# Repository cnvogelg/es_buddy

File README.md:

# es_buddy - EuroShield Add On Boards

EuroShield Buddy PCB Boards and Arduino Library.

  - [Teensy 4.0 Adapter](#teensy-40-adapter)
  - [Rotary Encoder Buddy Board](#rotary-encoder-buddy-board)
  - [LCD/OLED Display Buddy Board](#lcdoled-display-buddy-board)
  - [Twister Buddy Board](#twister-buddy-board)

You can combine these boards as you like.

Licensed by Creative Commons Attribution Share Alike 4.0 International

## Teensy 4.0 Adapter

Version: 1.1

This little adapter board allows to use a Teensy 4.0 board on your EuroShield 1 (short ES) eurorack module.

This is the required re-routing of the Pins:

| Teensy 3.x / EuroShield Pin | Teensy 4.x Pin | Description |
|-----------------------------|----------------|-------------|
| GND | GND | |
| 0 | 0 | Midi IN |
| 1 | 1 | Midi Out |
| 2 | 2 | Button on ES and on Rotary Encoder |
| 3 | 3 | LED 1 |
| 4 | 4 | LED 2 |
| 5 | 5 | LED 2 |
| 6 | 6 | LED 3 |
| 7 | 11 | SPI MOSI |
| 8 | 9 | Display Reset |
| 9 | 21 | Audio BCLK |
| 10 | 10 | SPI CS |
| 11 | 23 | Audio MCLK - A 100 Ohm Resistor is required here! |
| 12 | 12 | SPI MISO |

| Teensy 3.x / EuroShield Pin | Teensy 4.x Pin | Description |
|-----------------------------|----------------|-------------|
| VIN | VIN | |
| AGND | AGND | |
| 3.3V | 3.3V | |
| 23 | 20 | Audio LRCLK |
| 22 | 7 | Audio TX DIN |
| 21 | 15 | Lo Pot on ES |
| 20 | 14 | Hi Pot on ES |
| 19 | 19 | I2C SCL |
| 18 | 18 | I2C SDA |
| 17 | 17 | Rotary Encoder A |
| 16 | 16 | Rotary Encoder B |
| 15 | 22 | Display CMD/Data |
| 14 | 13 | SPI SCK |
| 13 | 8 | Audio RX DOUT |

All Pins are direclty connected expect Audio MCLK is connected via
a 100 Ohm resistor.

## Rotary Encoder Buddy Board

Version: 1.1

Add a rotary encoder with button to your Euroshield.

### BOM

| Symbol | Part | Description | Mouser No. |
|--------|------|-------------|------------|
| ROT1 | PEC12R-3220F-S0024 | Bourns Rotary Encoder | 652-PEC12R3220FS0024 |
| R1-R3 | SMD 0805 10k | 10k Resistor | 71-CRCW080510K0FKEAC |

## LCD/OLED Display Buddy Board

Version: 1.1

Add an SPI LCD or OLED display to your EuroShield. While the OLED with 
128 x 64 fits nicely into the form factor of the shield, the LCD is wider
and offers 160 x 128 colored pixels.

The LCD has the following parameters:

 - 160 x 128 color TFT LCD 1.8 Inch
 - SPI
 - ST 7735 Controller

| LCD Pin | Teensy 3.2 Pin | Description |
| ------- | ---------- | ----------- |
| 1 | GND | GND |
| 2 | 3.3V | 3.3V |
| 3 | 8  | Display Reset |
| 4 | 15 | Display Cmd/Data |
| 5 | -  | N/A |
| 6 | 10 | SPI CS |
| 7 | 7  | SPI MOSI |
| 8 | 14 | SPI SCK |
| 9 | 12 | SPI MISO |
| 10 | 3.3V | Display Light |

I use an Adafruit 1.8" Color TFT LCD display with MicroSD Card Breakout (358)

The OLED has the following parameters:

- 128 x 64 monochrome OLED 0.96 Inch
- SPI
- SSD 1306 Controller

| OLED Pin | Teensy 3.2 Pin | Description |
| ------- | ---------- | ----------- |
| 1 | 3.3V | 3.3V |
| 2 | GND | GND |
| 3 | -  | N/A|
| 4 | 7  | SPI MOSI |
| 5 | 14 | SPI SCK |
| 6 | 10 | SPI CS |
| 7 | 15 | Display Cmd/Data |
| 8 | 8  | Display Reset |

## Twister Buddy Board

Version: 1.0

Turn the Teensy around so that the USB connector points upwards and 
a connected USB cable gets out of the way and does not obstruct the display.

# Build Instructions

If you want to build the full stack of buddy boards:

1. Start with the display board and solder extra long header pins

2. First populate the rotary encoder board (resistors and the encoder) and 
  then solder the board below the display board

3. Prepare the Twister Board by adding headers to one side for a Teensy 4.0
  setup or a female connector for a Teensy 3.2. If you want to 
  use a Teensy 4.0 then add a female connector to the Teensy 4.0 side of the
  adapter:

4. Solder the prepared Twister Board on top of the Display Board. Make sure
  that the Teensy USB port on the top side points upwards:

5. For a Teensy 4.0 finally solder the Teensy 4.0 adapter board on top of
  the Twister Board. Note: make sure to add some space between the boards
  so that the Teensy 4.0 female connector pins do not touch the Display
  Board pins! Here a both variants: Teensy 4.0 and Teensy 3.2 boards

6. Finally add either a LCD or OLED display. Both display types work with 
  both Teensy CPUs.

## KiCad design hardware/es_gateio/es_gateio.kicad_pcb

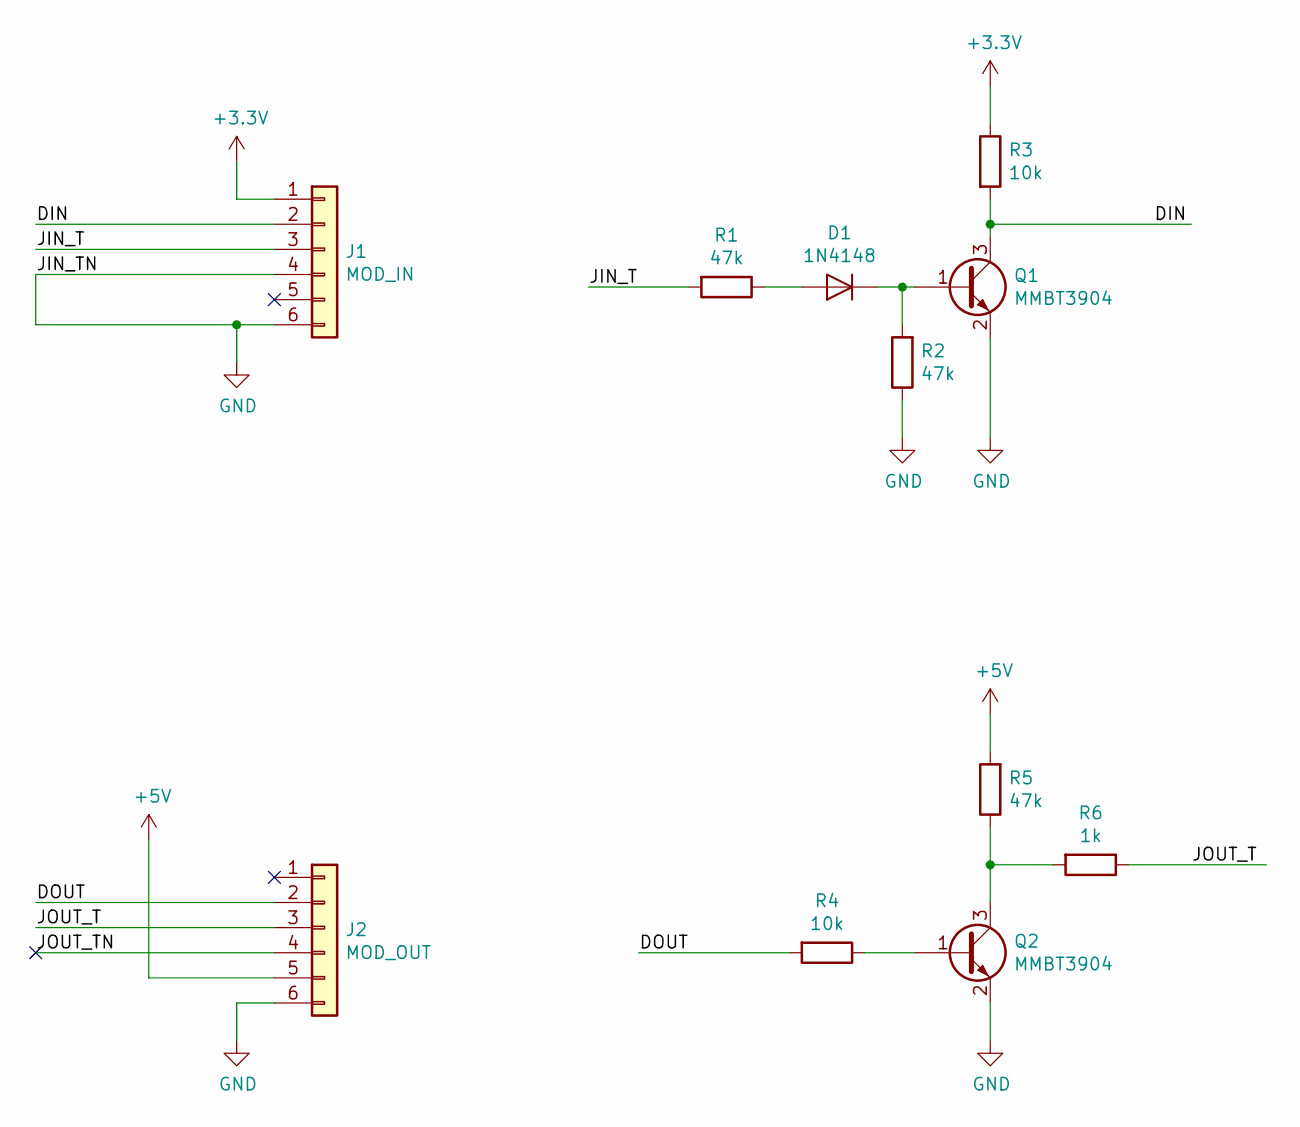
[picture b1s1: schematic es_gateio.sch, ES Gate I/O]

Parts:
D1: 1N4148; D_MiniMELF
J1: MOD_IN; PinHeader_2x03_P2.54mm_Vertical
J2: MOD_OUT; PinHeader_2x03_P2.54mm_Vertical
Q1, Q2: MMBT3904; SOT-23
R1, R2, R5: 47k; R_0805_2012Metric_Pad1.15x1.40mm_HandSolder
R3, R4: 10k; R_0805_2012Metric_Pad1.15x1.40mm_HandSolder
R6: 1k; R_0805_2012Metric_Pad1.15x1.40mm_HandSolder

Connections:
+3V3: J1.1, R3.1
+5V: J2.5, R5.2
/DIN: J1.2, Q1.3 (C), R3.2
/DOUT: J2.2, R4.2
/JIN_T: J1.3, R1.2
/JOUT_T: J2.3, R6.1
/JOUT_TN: J2.4
GND: J1.4, J1.6, J2.6, Q1.2 (E), Q2.2 (E), R2.1
unnamed: D1.1 (K), Q1.1 (B), R2.2
unnamed: D1.2 (A), R1.1
unnamed: Q2.1 (B), R4.1
unnamed: Q2.3 (C), R5.1, R6.2

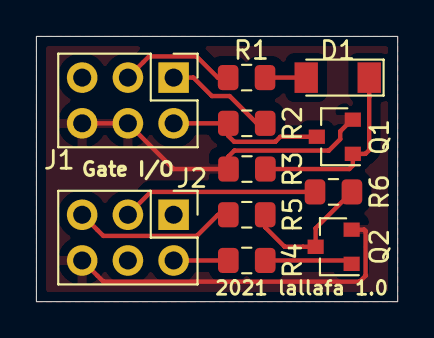
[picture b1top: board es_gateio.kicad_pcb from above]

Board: 2 copper layers, 20.1 x 14.7 mm, 11 parts (0 on the bottom side), 11 nets.

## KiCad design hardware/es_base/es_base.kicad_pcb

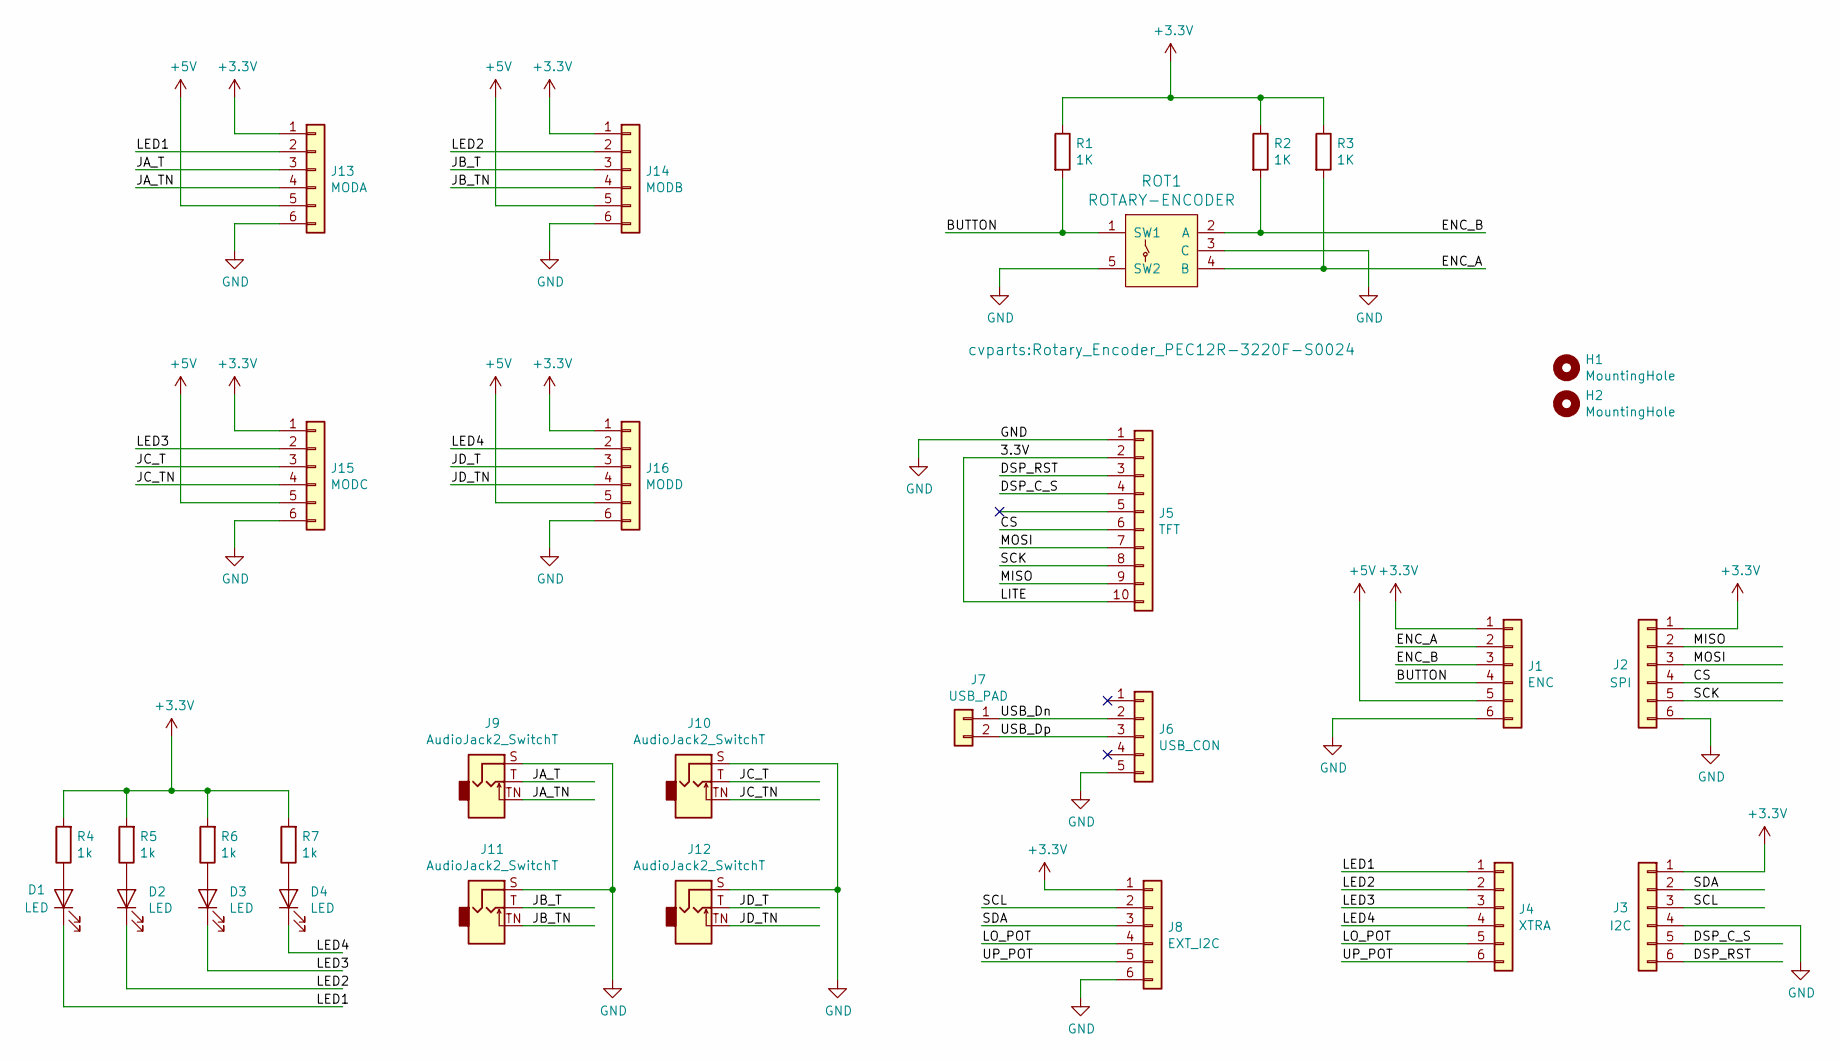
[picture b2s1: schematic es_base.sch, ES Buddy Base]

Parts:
D1, D2, D3, D4: LED; LED_D3.0mm
H1, H2: MountingHole; MountingHole_3.2mm_M3_ISO14580_Pad
J1: ENC; PinHeader_1x06_P2.54mm_Vertical
J2: SPI; PinHeader_1x06_P2.54mm_Vertical
J3: I2C; PinHeader_1x06_P2.54mm_Vertical
J4: XTRA; PinHeader_1x06_P2.54mm_Vertical
J5: TFT; PinHeader_1x10_P2.54mm_Vertical
J6: USB_CON; PinHeader_1x05_P2.54mm_Vertical
J7: USB_PAD; PinHeader_1x02_P2.54mm_Vertical
J8: EXT_I2C; PinHeader_2x03_P2.54mm_Vertical
J9, J10, J11, J12: AudioJack2_SwitchT; Jack_3.5mm_QingPu_WQP-PJ398SM_Vertical_CircularHoles
J13: MODA; PinHeader_2x03_P2.54mm_Vertical
J14: MODB; PinHeader_2x03_P2.54mm_Vertical
J15: MODC; PinHeader_2x03_P2.54mm_Vertical
J16: MODD; PinHeader_2x03_P2.54mm_Vertical
R1, R2, R3: 1K; R_0805_2012Metric_Pad1.15x1.40mm_HandSolder
R4, R5, R6, R7: 1k; R_0805_2012Metric_Pad1.15x1.40mm_HandSolder
ROT1: ROTARY-ENCODER; Rotary_Encoder_PEC12R-3220F-S0024

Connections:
+3V3: J1.1, J2.1, J3.1, J8.1, J13.1, J14.1, J15.1, J16.1, R1.1, R2.1, R3.1, R4.2, R5.2, R6.2, R7.2
+5V: J1.5, J13.5, J14.5, J15.5, J16.5
/3.3V: J5.2, J5.10
/BUTTON: J1.4, R1.2, ROT1.1 (SW1)
/CS: J2.4, J5.6
/DSP_C_S: J3.5, J5.4
/DSP_RST: J3.6, J5.3
/ENC_A: J1.2, R3.2, ROT1.4 (B)
/ENC_B: J1.3, R2.2, ROT1.2 (A)
/JA_T: J9.T, J13.3
/JA_TN: J9.TN, J13.4
/JB_T: J11.T, J14.3
/JB_TN: J11.TN, J14.4
/JC_T: J10.T, J15.3
/JC_TN: J10.TN, J15.4
/JD_T: J12.T, J16.3
/JD_TN: J12.TN, J16.4
/LED1: D1.1 (K), J4.1, J13.2
/LED2: D2.1 (K), J4.2, J14.2
/LED3: D3.1 (K), J4.3, J15.2
/LED4: D4.1 (K), J4.4, J16.2
/LO_POT: J4.5, J8.4
/MISO: J2.2, J5.9
/MOSI: J2.3, J5.7
/SCK: J2.5, J5.8
/SCL: J3.3, J8.2
/SDA: J3.2, J8.3
/UP_POT: J4.6, J8.5
/USB_Dn: J6.2, J7.1
/USB_Dp: J6.3, J7.2
GND: J1.6, J2.6, J3.4, J5.1, J6.5, J8.6, J9.S, J10.S, J11.S, J12.S, J13.6, J14.6, J15.6, J16.6, ROT1.3 (C), ROT1.5 (SW2)
unnamed: D1.2 (A), R4.1
unnamed: D2.2 (A), R5.1
unnamed: D3.2 (A), R6.1
unnamed: D4.2 (A), R7.1

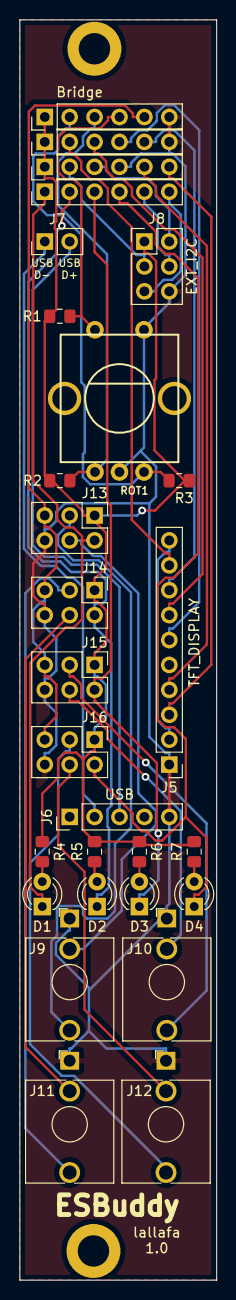
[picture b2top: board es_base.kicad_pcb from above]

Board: 2 copper layers, 20.1 x 128.5 mm, 30 parts (0 on the bottom side), 35 nets.

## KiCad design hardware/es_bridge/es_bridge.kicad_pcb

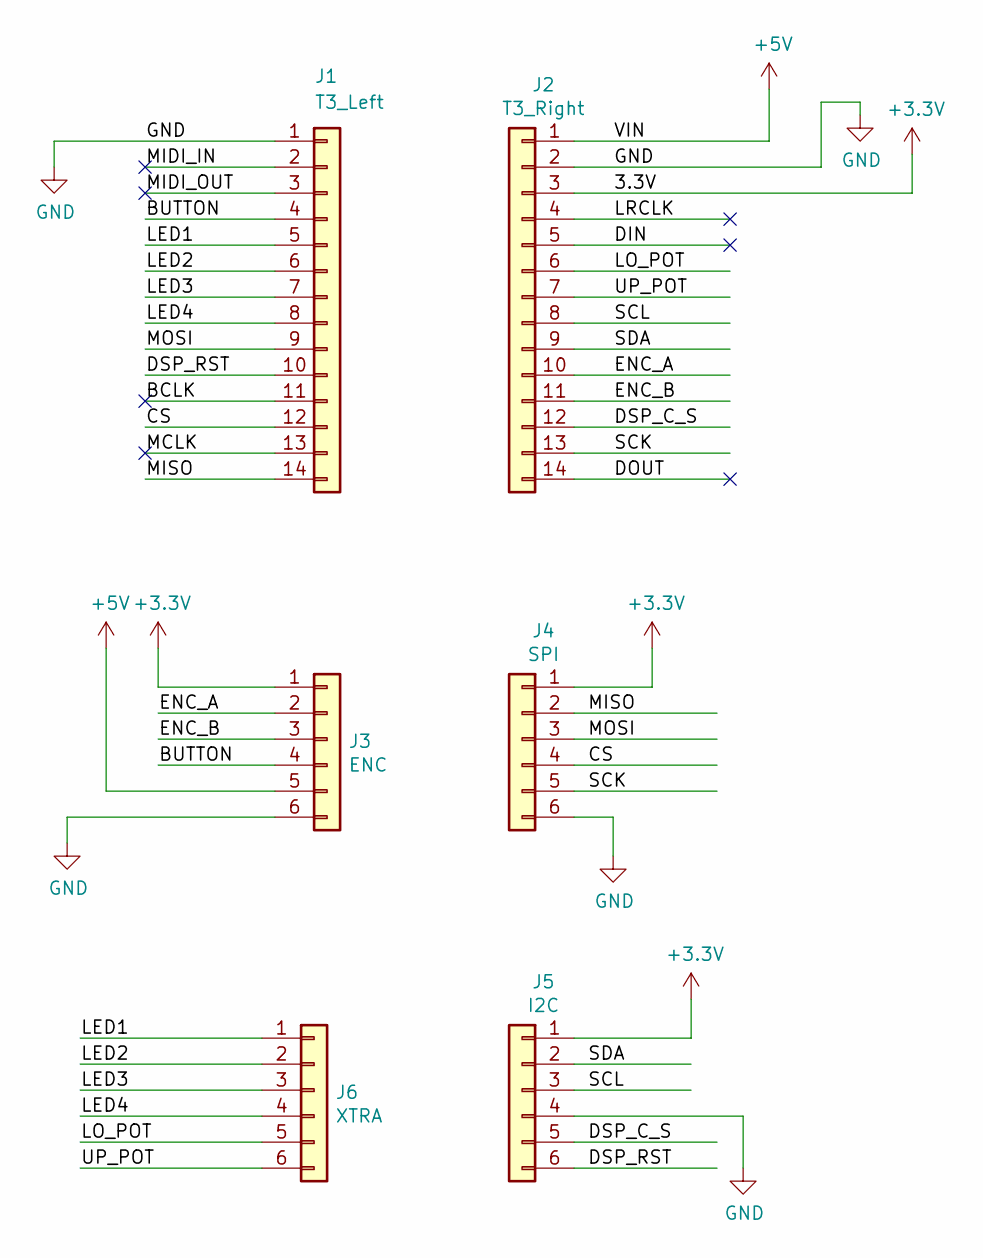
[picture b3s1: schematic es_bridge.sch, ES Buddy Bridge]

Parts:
J1: T3_Left; PinHeader_1x14_P2.54mm_Vertical_NoSilk
J2: T3_Right; PinHeader_1x14_P2.54mm_Vertical_NoSilk_NoPin1
J3: ENC; PinHeader_1x06_P2.54mm_Vertical
J4: SPI; PinHeader_1x06_P2.54mm_Vertical
J5: I2C; PinHeader_1x06_P2.54mm_Vertical
J6: XTRA; PinHeader_1x06_P2.54mm_Vertical

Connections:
+3V3: J2.3, J3.1, J4.1, J5.1
+5V: J2.1, J3.5
/BCLK: J1.11
/BUTTON: J1.4, J3.4
/CS: J1.12, J4.4
/DIN: J2.5
/DOUT: J2.14
/DSP_C_S: J2.12, J5.5
/DSP_RST: J1.10, J5.6
/ENC_A: J2.10, J3.2
/ENC_B: J2.11, J3.3
/LED1: J1.5, J6.1
/LED2: J1.6, J6.2
/LED3: J1.7, J6.3
/LED4: J1.8, J6.4
/LO_POT: J2.6, J6.5
/LRCLK: J2.4
/MCLK: J1.13
/MIDI_IN: J1.2
/MIDI_OUT: J1.3
/MISO: J1.14, J4.2
/MOSI: J1.9, J4.3
/SCK: J2.13, J4.5
/SCL: J2.8, J5.3
/SDA: J2.9, J5.2
/UP_POT: J2.7, J6.6
GND: J1.1, J2.2, J3.6, J4.6, J5.4

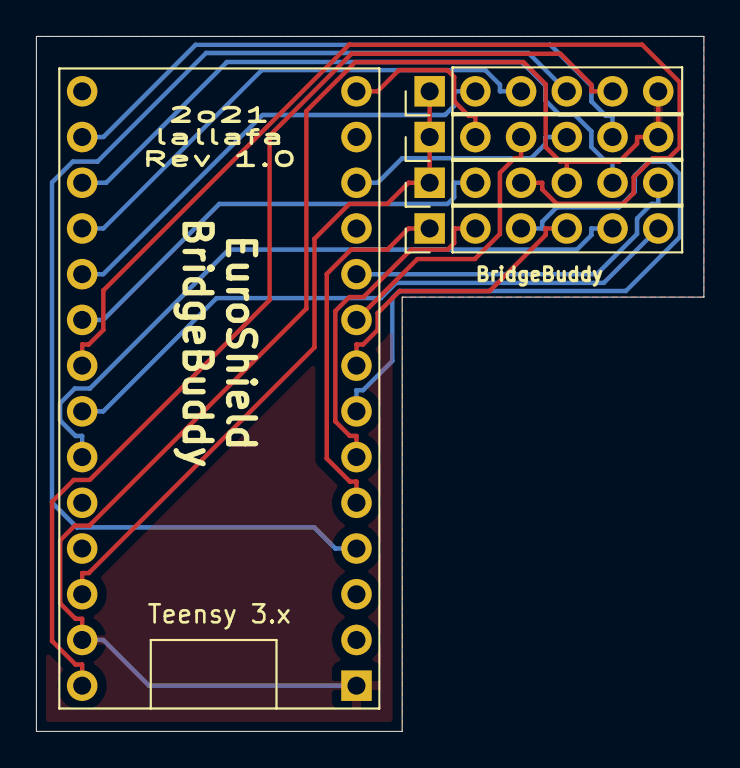
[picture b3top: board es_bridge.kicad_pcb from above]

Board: 2 copper layers, 37.1 x 38.6 mm, 6 parts (0 on the bottom side), 20 nets.

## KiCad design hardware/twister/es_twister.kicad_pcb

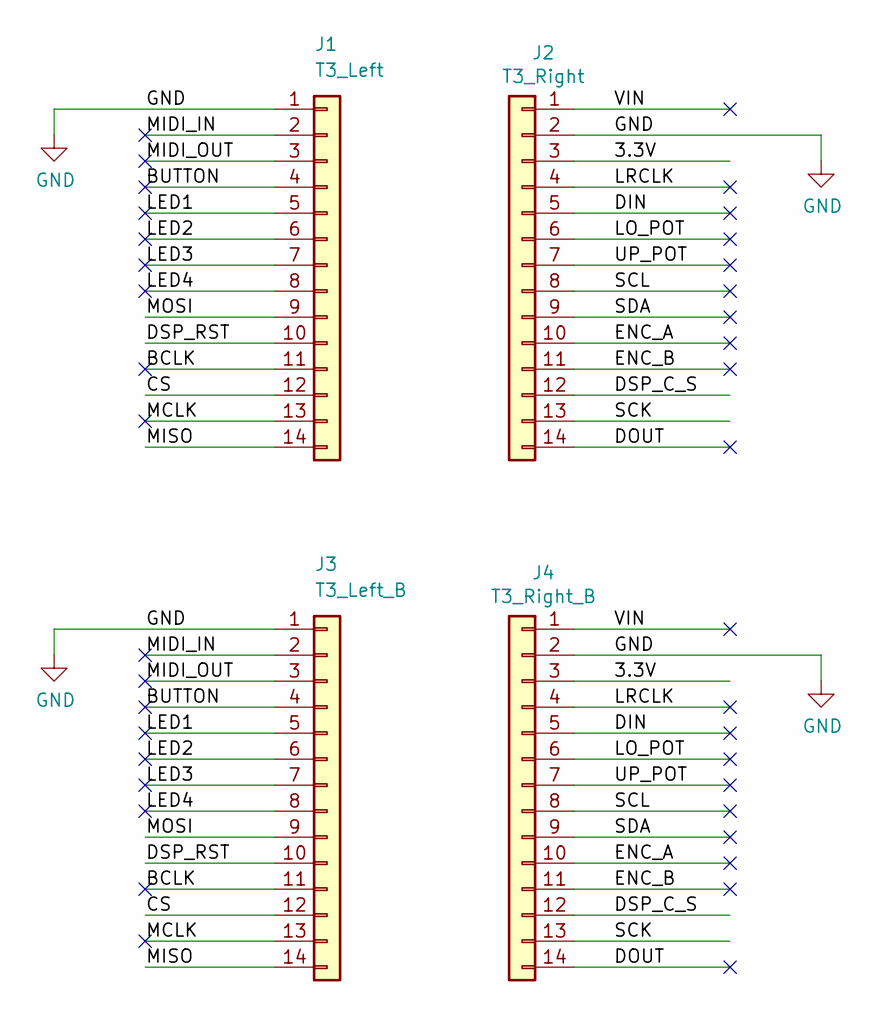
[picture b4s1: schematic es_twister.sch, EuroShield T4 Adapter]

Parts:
J1: T3_Left; PinHeader_1x14_P2.54mm_Vertical_NoSilk
J2: T3_Right; PinHeader_1x14_P2.54mm_Vertical_NoSilk_NoPin1
J3: T3_Left_B; PinHeader_1x14_P2.54mm_Vertical_NoSilk
J4: T3_Right_B; PinHeader_1x14_P2.54mm_Vertical_NoSilk_NoPin1

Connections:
/3.3V: J2.3, J4.3
/BCLK: J1.11, J3.11
/BUTTON: J1.4, J3.4
/CS: J1.12, J3.12
/DIN: J2.5, J4.5
/DOUT: J2.14, J4.14
/DSP_C_S: J2.12, J4.12
/DSP_RST: J1.10, J3.10
/ENC_A: J2.10, J4.10
/ENC_B: J2.11, J4.11
/LED1: J1.5, J3.5
/LED2: J1.6, J3.6
/LED3: J1.7, J3.7
/LED4: J1.8, J3.8
/LO_POT: J2.6, J4.6
/LRCLK: J2.4, J4.4
/MCLK: J1.13, J3.13
/MIDI_IN: J1.2, J3.2
/MIDI_OUT: J1.3, J3.3
/MISO: J1.14, J3.14
/MOSI: J1.9, J3.9
/SCK: J2.13, J4.13
/SCL: J2.8, J4.8
/SDA: J2.9, J4.9
/UP_POT: J2.7, J4.7
/VIN: J2.1, J4.1
GND: J1.1, J2.2, J3.1, J4.2

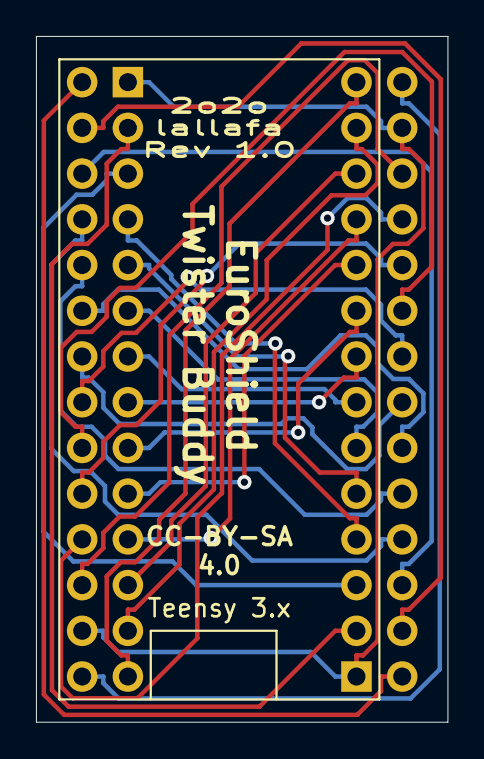
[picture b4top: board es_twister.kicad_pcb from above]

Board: 2 copper layers, 22.9 x 38.1 mm, 4 parts (0 on the bottom side), 27 nets.

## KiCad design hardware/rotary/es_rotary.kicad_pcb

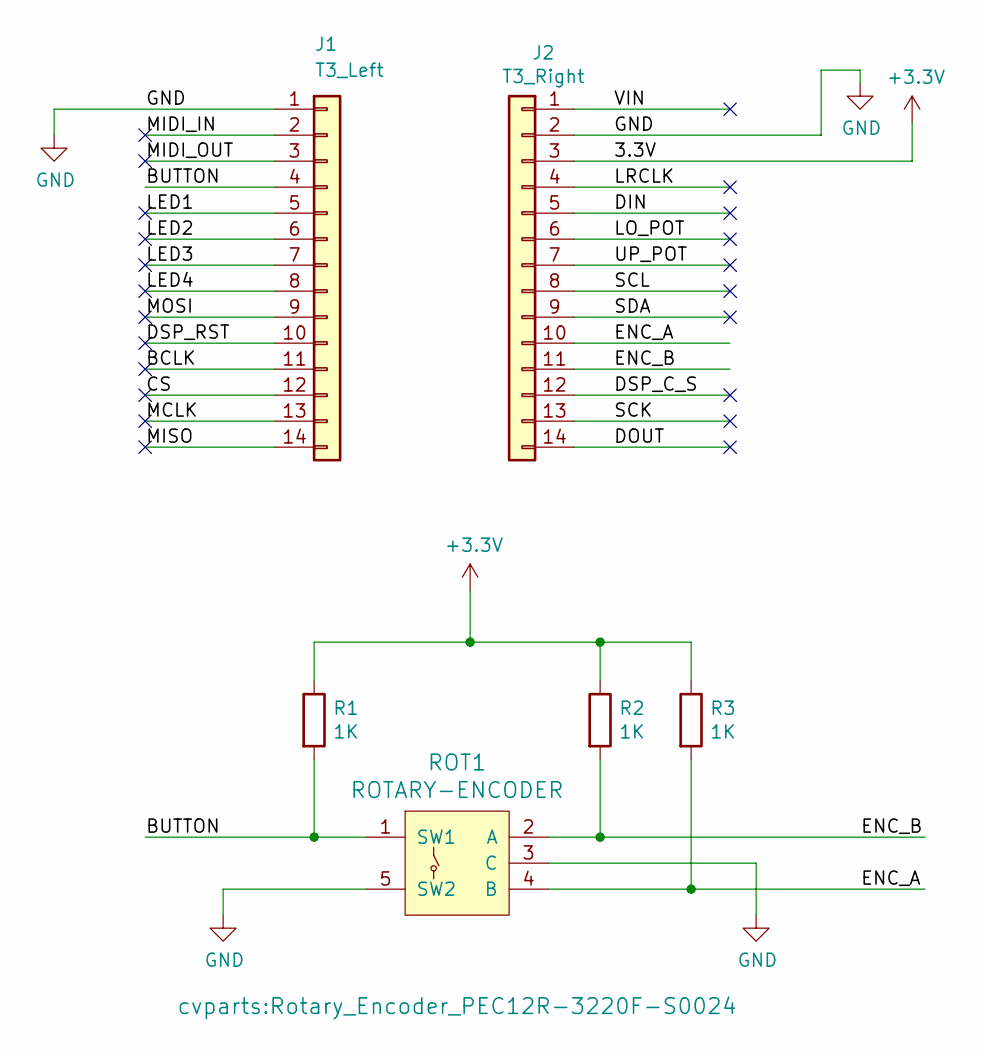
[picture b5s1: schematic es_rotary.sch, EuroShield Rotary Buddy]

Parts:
J1: T3_Left; PinHeader_1x14_P2.54mm_Vertical_NoSilk
J2: T3_Right; PinHeader_1x14_P2.54mm_Vertical_NoSilk_NoPin1
R1, R2, R3: 1K; R_0805_2012Metric_Pad1.15x1.40mm_HandSolder
ROT1: ROTARY-ENCODER; Rotary_Encoder_PEC12R-3220F-S0024

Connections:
+3V3: J2.3, R1.1, R2.1, R3.1
/BCLK: J1.11
/BUTTON: J1.4, R1.2, ROT1.1 (SW1)
/CS: J1.12
/DIN: J2.5
/DOUT: J2.14
/DSP_C_S: J2.12
/DSP_RST: J1.10
/ENC_A: J2.10, R3.2, ROT1.4 (B)
/ENC_B: J2.11, R2.2, ROT1.2 (A)
/LED1: J1.5
/LED2: J1.6
/LED3: J1.7
/LED4: J1.8
/LO_POT: J2.6
/LRCLK: J2.4
/MCLK: J1.13
/MIDI_IN: J1.2
/MIDI_OUT: J1.3
/MISO: J1.14
/MOSI: J1.9
/SCK: J2.13
/SCL: J2.8
/SDA: J2.9
/UP_POT: J2.7
/VIN: J2.1
GND: J1.1, J2.2, ROT1.3 (C), ROT1.5 (SW2)

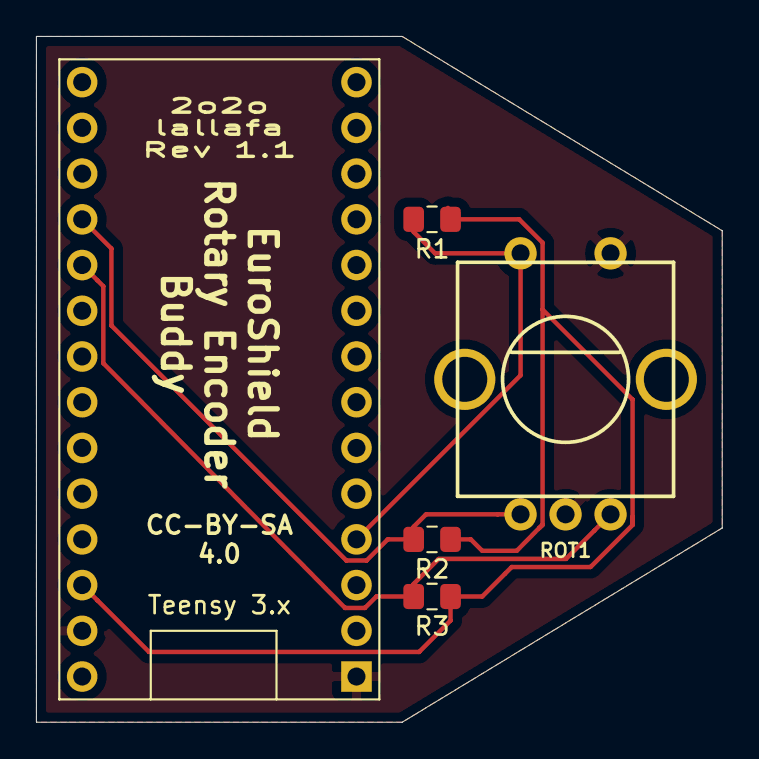
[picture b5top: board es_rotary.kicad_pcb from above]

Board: 2 copper layers, 38.1 x 38.1 mm, 6 parts (0 on the bottom side), 5 nets.

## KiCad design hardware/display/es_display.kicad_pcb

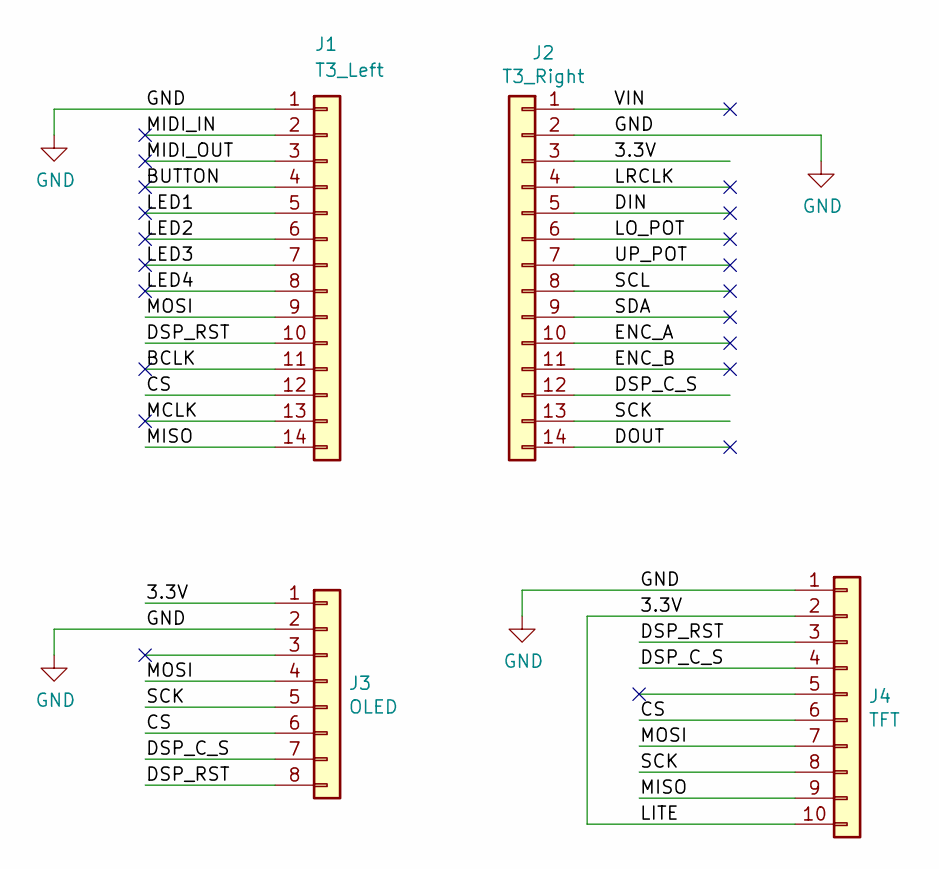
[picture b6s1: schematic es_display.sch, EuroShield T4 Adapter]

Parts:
J1: T3_Left; PinHeader_1x14_P2.54mm_Vertical_NoSilk
J2: T3_Right; PinHeader_1x14_P2.54mm_Vertical_NoSilk_NoPin1
J3: OLED; PinHeader_1x08_P2.54mm_Vertical
J4: TFT; PinHeader_1x10_P2.54mm_Vertical

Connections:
/3.3V: J2.3, J3.1, J4.2, J4.10
/BCLK: J1.11
/BUTTON: J1.4
/CS: J1.12, J3.6, J4.6
/DIN: J2.5
/DOUT: J2.14
/DSP_C_S: J2.12, J3.7, J4.4
/DSP_RST: J1.10, J3.8, J4.3
/ENC_A: J2.10
/ENC_B: J2.11
/LED1: J1.5
/LED2: J1.6
/LED3: J1.7
/LED4: J1.8
/LO_POT: J2.6
/LRCLK: J2.4
/MCLK: J1.13
/MIDI_IN: J1.2
/MIDI_OUT: J1.3
/MISO: J1.14, J4.9
/MOSI: J1.9, J3.4, J4.7
/SCK: J2.13, J3.5, J4.8
/SCL: J2.8
/SDA: J2.9
/UP_POT: J2.7
/VIN: J2.1
GND: J1.1, J2.2, J3.2, J4.1

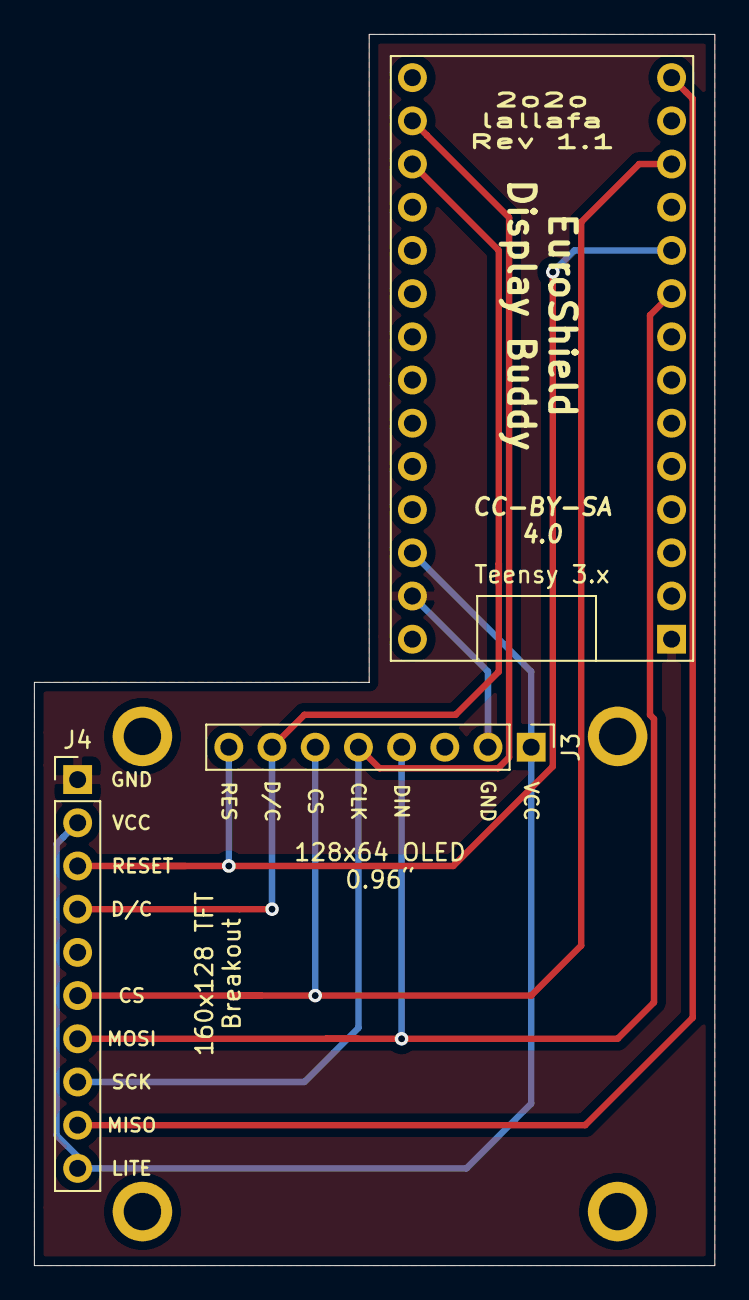
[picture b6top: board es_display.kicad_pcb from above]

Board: 2 copper layers, 40.0 x 72.4 mm, 8 parts (0 on the bottom side), 8 nets.

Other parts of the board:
Pad1, Pad2, Pad3, Pad4: MountingHole_2.2mm_M2_ISO7380_Pad

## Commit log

2020-09-26 added t4 adapter
2020-09-26 added display
2020-09-26 added rotary
2020-10-09 added t4 pin mapping
2020-10-09 updated rot and display to v1.1
2020-10-09 added twister
2020-10-10 started Arduino lib
2020-10-11 restructured and fixes
2020-10-11 added io test examples
2020-10-22 set license: CC-BY-SA-4.0
2020-11-02 added images and more README
2020-11-02 fixed link
2020-11-02 updated rotary gerbers
2020-11-07 added midi usb examples
2020-11-19 added audio usb example
2020-11-24 started scope demo
2020-11-26 added text attributes
2020-11-26 introduced sample array
2020-11-26 use double buffering for avg sampling
2020-11-27 improved scope widget
2020-12-04 added param widget
2020-12-12 filled scene
2020-12-12 handle events
2020-12-22 prepare scene selector
2020-12-23 fixed scene control
2020-12-23 restructured code
2021-01-19 add minmax
2021-02-03 fixed es audio setup
2021-02-04 fix build
2021-02-04 started spectrum widget
2021-02-25 draw spectrum
2021-02-25 auto hide controls
2021-02-25 cleaned up scope
2021-02-25 add audio_signal.h
2021-02-25 added widget show mode
2021-02-25 better ui control
2021-03-13 added new hardware: bridge, base board, and gateio
